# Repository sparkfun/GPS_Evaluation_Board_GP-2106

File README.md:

**NOTE:** *This product has been retired from our catalog. If you are looking for more up-to-date info, please check out some of these resources to see how other users are still hacking and improving on this product.*
* *[SparkFun Forum](https://forum.sparkfun.com/)*
* *[Comments Here on GitHub](https://github.com/sparkfun/GPS_Evaluation_Board_GP-2106/issues)*
* *[IRC Channel](https://www.sparkfun.com/news/263)*

SparkFun GPS Evaluation Board - GP-2106
========================================

[*SparkFun GPS Evaluation Board - GP-2106 (GPS-10995)*](https://www.sparkfun.com/products/10995)

The GP-2106 Evaluation Board features everything you need to get the [GP-2106 module](https://www.sparkfun.com/products/retired/10890) talking to your system. 
Because the GP-2106 is a 1.8V module, we’ve provided level-shifting for 3.3 and 5V systems. 
The board also features a PPS status LED, on/off button and an FTDI Basic compatible header!

Repository Contents
-------------------

* **/Hardware** - Eagle design files (.brd, .sch)
* **/Production** - Production panel files (.brd)

Documentation
--------------
* **[SparkFun Fritzing repo](https://github.com/sparkfun/Fritzing_Parts)** - Fritzing diagrams for SparkFun products.
* **[SparkFun 3D Model repo](https://github.com/sparkfun/3D_Models)** - 3D models of SparkFun products. 

License Information
-------------------
This product is _**open source**_! 

The **hardware** is released under [Creative Commons ShareAlike 4.0 International](https://creativecommons.org/licenses/by-sa/4.0/).

Please use, reuse, and modify these files as you see fit. Please maintain attribution to SparkFun Electronics and release anything derivative under the same license.

Distributed as-is; no warranty is given.

- Your friends at SparkFun.

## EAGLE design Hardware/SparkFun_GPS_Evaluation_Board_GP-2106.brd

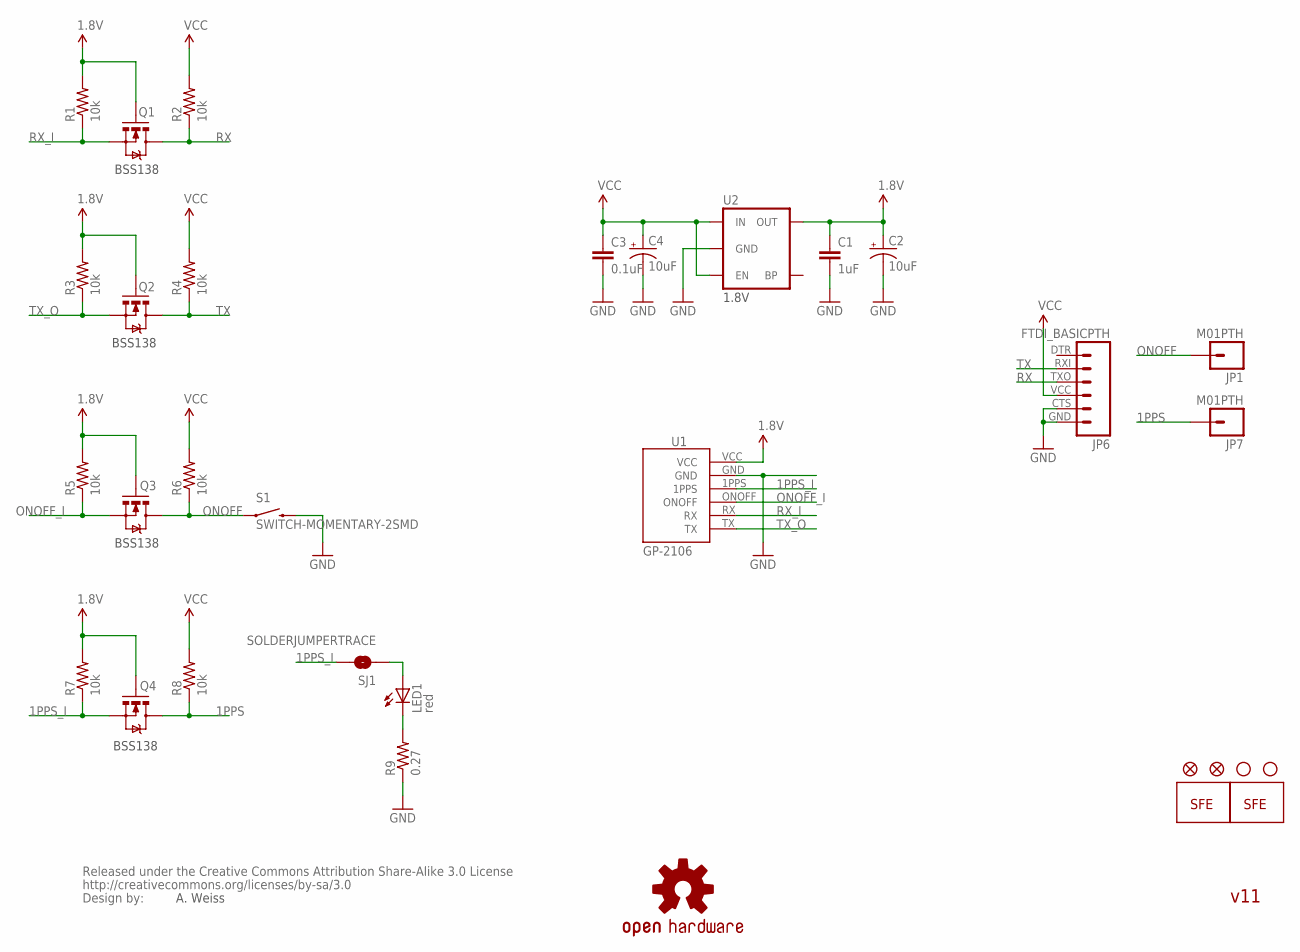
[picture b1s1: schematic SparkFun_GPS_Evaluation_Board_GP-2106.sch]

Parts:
C1: 1uF; 0402-CAP
C2, C4: 10uF; EIA3216
C3: 0.1uF; 0402-CAP
JP1, JP7: M01PTH; 1X01
JP2, JP3: STAND-OFF
JP4: LOGO-SFESK; SFE-LOGO-FLAME
JP5: LOGO-SFENEW; SFE-NEW-WEBLOGO
JP6: FTDI_BASICPTH; FTDI_BASIC
JP8, JP9: FIDUCIALUFIDUCIAL; MICRO-FIDUCIAL
LED1: red; LED-0603
Q1, Q2, Q3, Q4: MOSFET-NCHANNELSMD; SOT23-3
R1, R2, R3, R4, R5, R6, R7, R8: 10k; 0402-RES
R9: 0.27; 0402-RES
S1: SWITCH-MOMENTARY-2SMD; TACTILE_SWITCH_SMD
SJ1: SOLDERJUMPERTRACE; SJ_2S-TRACE
U1: GP-2106
U2: V_REG_LDOSMD2; SC70
U$7: OSHW-LOGOS; OSHW-LOGO-S
U$8: CREATIVE_COMMONS

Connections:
1.8V: C1.1, C2.A (+), Q1.1 (G), Q2.1 (G), Q3.1 (G), Q4.1 (G), R1.2, R3.2, R5.2, R7.2, U1.VCC, U2.5 (OUT)
1PPS: JP7.1, Q4.3 (D), R8.1
1PPS_I: Q4.2 (S), R7.1, SJ1.2, U1.1PPS
GND: C1.2, C2.C (-), C3.2, C4.C (-), JP6.CTS (5), JP6.GND (6), R9.1, S1.3 (2), U1.GND, U2.2 (GND)
unnamed: LED1.C, R9.2
unnamed: LED1.A, SJ1.1
ONOFF: JP1.1, Q3.3 (D), R6.1, S1.1
ONOFF_I: Q3.2 (S), R5.1, U1.ONOFF
RX: JP6.TXO (3), Q1.3 (D), R2.1
RX_I: Q1.2 (S), R1.1, U1.RX
TX: JP6.RXI (2), Q2.3 (D), R4.1
TX_O: Q2.2 (S), R3.1, U1.TX
VCC: C3.1, C4.A (+), JP6.VCC (4), R2.2, R4.2, R6.2, R8.2, U2.1 (IN), U2.3 (EN)

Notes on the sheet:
1.8V
BSS138
A. Weiss
v11

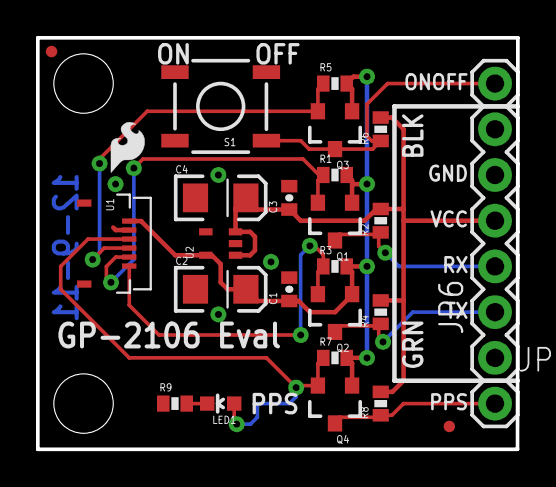
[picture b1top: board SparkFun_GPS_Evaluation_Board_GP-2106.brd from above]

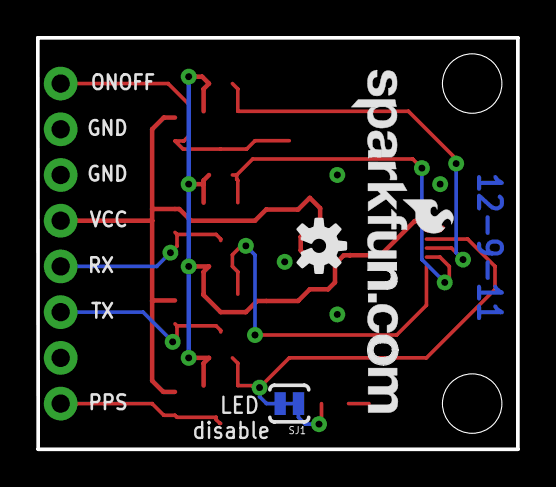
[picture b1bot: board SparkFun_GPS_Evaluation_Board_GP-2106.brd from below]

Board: 2 copper layers, 26.7 x 22.9 mm, 33 parts (3 on the bottom side), 13 nets.

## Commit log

2015-05-12 Adding hardware

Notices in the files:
parts and their libraries:
SparkFun: Released under the Creative Commons Attribution Share-Alike 3.0 License
SparkFun: http://creativecommons.org/licenses/by-sa/3.0
